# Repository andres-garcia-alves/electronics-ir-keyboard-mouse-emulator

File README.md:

# IR Keyboard+Mouse Emulator

Electronic project for use a IR Remote Control to control a Home Theater PC (HTPC) based on Arduino PRO Micro.  
Schematics diagram + PCB diagram (KiCAD 9) and case 3D model (Blender) are also provided.

This project comes in two versions: `Allways On` and `Low Power`.  
**Very important**: the current status of the `Low Power` version is **not working**, maybe I'll give it another try in the future.

- The `Allways On` version provides an immediate response when a remote control button is pressed.  
However, the gadget will constantly draw approximately 35-40mA from the USB port.

- The `Low Power` version automatically powers down the device after 30 seconds of inactivity, and it powers back on upon receiving an IR signal.  
This allows the gadget's power consumption to drop 99% of the time to ~1mA (the consumption of the IR sensor, the only component that remains powered on).  
However, due to the power-up time and the wait for the PC to recognize the device, there is a slight delay before it can be used.  
A high-side topology is used to power down the Arduino.
  - Hardware Variant A: External connection with a USB-A cable to J1 (USB-A socket).  
    Use a 2-strand cable from J2 (2-pins header) to the USB jack of Arduino for **data only** (D+/D-).
  - Hardware Variant B: External connection with a USB-B mini/micro cable to Arduino.  
    Cut the VCC wire of USB-B cable and pass it through J1 (2-pins header).

&nbsp;

General commands:
- Key Lock/Unlock (to avoid collition with regular TV usage).
- Key Esc
- Key Close (close current program)
- Mouse Change Speed
- Mouse Left Click
- Mouse Right Click
- Mouse MoveUp
- Mouse Move Right
- Mouse MoveDown
- Mouse MoveLeft

Media commands
- Media Player (open VLC media player)
- Media Play/Pause
- Media Stop
- Media Forward (moves forward 10 seconds)
- Media Rewind (moves backwards 10 seconds)
- Media Previous (moves forward 1 minute)
- Media Next (moves backwards 1 minute)
- Media Volume Mute
- Media Volume Up
- Media Volume Down

Miscellaneous commands
- MyPC (opens MyPC)
- Calculator (open Calculator);

Features:
- Dump of IR Codes (protocols: RC5, RC6, NEC, SONY, PANASONIC, LG, JVC, WHYNTER)

Benchmarks:

| Arduino PRO Micro                 | Tipical consumption |
|-----------------------------------|---------------------|
| Normal mode                       |            37-38 mA |
| ADC + SPI + TWI disabled          |            35-36 mA |
| USB detach + Clock @2 MHz         |            19-20 mA |
| USB detach + SLEEP_MODE_PWR_DOWN  |              4-5 mA |

I am currently working on incorporating a hardware low-power version.

&nbsp;

The `Allways ON` version uses the following electronic components:
- 1 x Arduino PRO Micro
- 1 x IR Receiver VS1838
- 1 x LED 3mm
- 1 x 1k ohm resistor

The `Low Power` version uses the following electronic components:
- 1 x Arduino PRO Micro
- 1 x IR Receiver VS1838
- 1 x LED 3mm
- 1 x 1k ohm resistor
- 1 x 47k ohm resistor
- 2 x 10k ohm resistor
- 1 x 100k ohm resistor
- 2 x 4.7k ohm resistor
- 3 x 1N4148 schottky diode
- 1 x 10uF electrolitic capacitor
- 3 x BC547 PNP transistor
- 2 x BC557 NPN transistor
- 1 x USB Type-A female connector
- 1 x Bornier 2-pins / JST connector 2-pins

&nbsp;

### Version Allways On

| Breadboard                                            | Assembly                                              |
|-------------------------------------------------------|-------------------------------------------------------|
|            |              |

| Schematics Diagram                                    | PCB Diagram                                           |
|-------------------------------------------------------|-------------------------------------------------------|
|    |           |

| PCB Render 3D                                         | PCB Render 3D                                         |
|-------------------------------------------------------|-------------------------------------------------------|
|   |    |

| Case 3D Model                                         | Project Final                                         |
|-------------------------------------------------------|-------------------------------------------------------|
|         |                     |

&nbsp;

### Version Low-Power-B

| Breadboard                                            | Assembly                                              |
|-------------------------------------------------------|-------------------------------------------------------|
|           |          |

| Assembly                                              | Assembly                                              |
|-------------------------------------------------------|-------------------------------------------------------|
|          |          |

| Schematics Diagram                                    | PCB Diagram                                           |
|-------------------------------------------------------|-------------------------------------------------------|
|   |          |

| PCB Render 3D                                         | PCB Render 3D                                         |
|-------------------------------------------------------|-------------------------------------------------------|
|  |   |

| Case 3D Model                                         | Project Final                                         |
|-------------------------------------------------------|-------------------------------------------------------|
|        |                     |

See 'Rescources' sub-folder for more pictures & videos of the project.

&nbsp;

### Version History

v1.00 (2025.12.18) - Initial release.  
v1.01 (2025.12.19) - Adding case 3D model.  
v1.02 (2025.12.22) - Update schematics and PCB.  
v1.03 (2025.12.29) - Firmware refactor for code clean-up.  
v1.04 (2026.01.02) - Adding Low-Power-A version protoboard & schematics.  
v1.05 (2026.01.03) - Adding Low-Power-A version firmware.  
v1.06 (2026.01.04) - Adding Low-Power-A version PCB.  
v1.07 (2026.01.04) - Adding Low-Power-A case 3D model.  
v1.08 (2026.01.06) - Minor fixes on Low-Power-A case 3D model.  
v1.09 (2026.01.09) - Minor fixes on Low-Power-A PCB.  
v1.10 (2026.01.14) - Adding Low-Power-B version schematics & PCB.  
v1.11 (2026.01.15) - Adding Low-Power-B 3D model.  
v1.12 (2026.01.18) - Minor fixes on Low-Power-B 3D model.  

&nbsp;

This source code is licensed under GPL v3.0  
Please send me your feedback about this project: andres.garcia.alves@gmail.com

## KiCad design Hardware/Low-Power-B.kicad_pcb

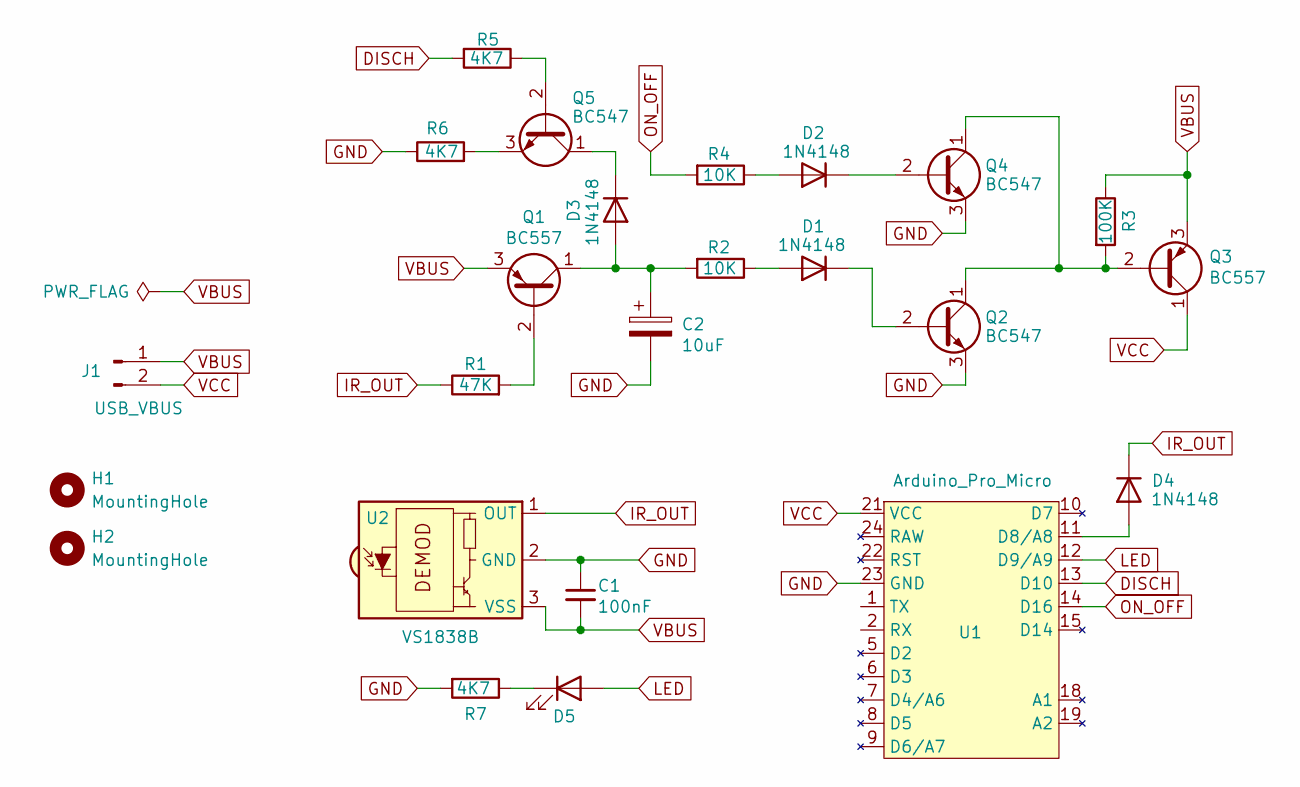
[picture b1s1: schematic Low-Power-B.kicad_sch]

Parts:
C1: 100nF; C_Disc_D6.0mm_W2.5mm_P5.00mm; Voltage 1kV; Tolerance 100%
C2: 10uF; CP_Radial_D5.0mm_P2.50mm
D1, D2, D3, D4: 1N4148; D_DO-35_SOD27_P7.62mm_Horizontal
D5: LED; LED_D5.0mm
H1, H2: MountingHole; MountingHole_2.2mm_M2_ISO7380
J1: USB_VBUS; JST_EH_B2B-EH-A_1x02_P2.50mm_Vertical
Q1, Q3: BC557; TO-92_Inline_Wide
Q2, Q4, Q5: BC547; TO-92_Inline_Wide
R1: 47K; R_Axial_DIN0207_L6.3mm_D2.5mm_P2.54mm_Vertical
R2: 10K; R_Axial_DIN0207_L6.3mm_D2.5mm_P7.62mm_Horizontal
R3: 100K; R_Axial_DIN0207_L6.3mm_D2.5mm_P2.54mm_Vertical
R4: 10K; R_Axial_DIN0207_L6.3mm_D2.5mm_P2.54mm_Vertical
R5, R6: 4K7; R_Axial_DIN0207_L6.3mm_D2.5mm_P2.54mm_Vertical
R7: 4K7; R_Axial_DIN0204_L3.6mm_D1.6mm_P7.62mm_Horizontal
U1: Arduino_Pro_Micro
U2: VS1838B; Vishay_MINICAST-3Pin

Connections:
DISCH: R5.2, U1.13 (D10)
GND: C1.1, C2.2, Q2.3 (E), Q4.3 (E), R6.1, R7.2, U1.3 (GND), U1.4 (GND), U1.23 (GND), U2.2 (GND)
IR_OUT: D4.1 (K), R1.1, U2.1 (OUT)
LED: D5.2 (A), U1.12 (D9/A9)
unnamed: D1.2 (A), R2.1
unnamed: D1.1 (K), Q2.2 (B)
unnamed: D2.2 (A), R4.1
unnamed: D2.1 (K), Q4.2 (B)
unnamed: C2.1, D3.2 (A), Q1.1 (C), R2.2
unnamed: D3.1 (K), Q5.1 (C)
unnamed: D4.2 (A), U1.11 (D8/A8)
unnamed: D5.1 (K), R7.1
unnamed: Q1.2 (B), R1.2
unnamed: Q2.1 (C), Q3.2 (B), Q4.1 (C), R3.2
unnamed: Q5.2 (B), R5.1
unnamed: Q5.3 (E), R6.2
ON_OFF: R4.2, U1.14 (D16)
VBUS: C1.2, J1.1, Q1.3 (E), Q3.3 (E), R3.1, U2.3 (VSS)
VCC: J1.2, Q3.1 (C), U1.21 (VCC)

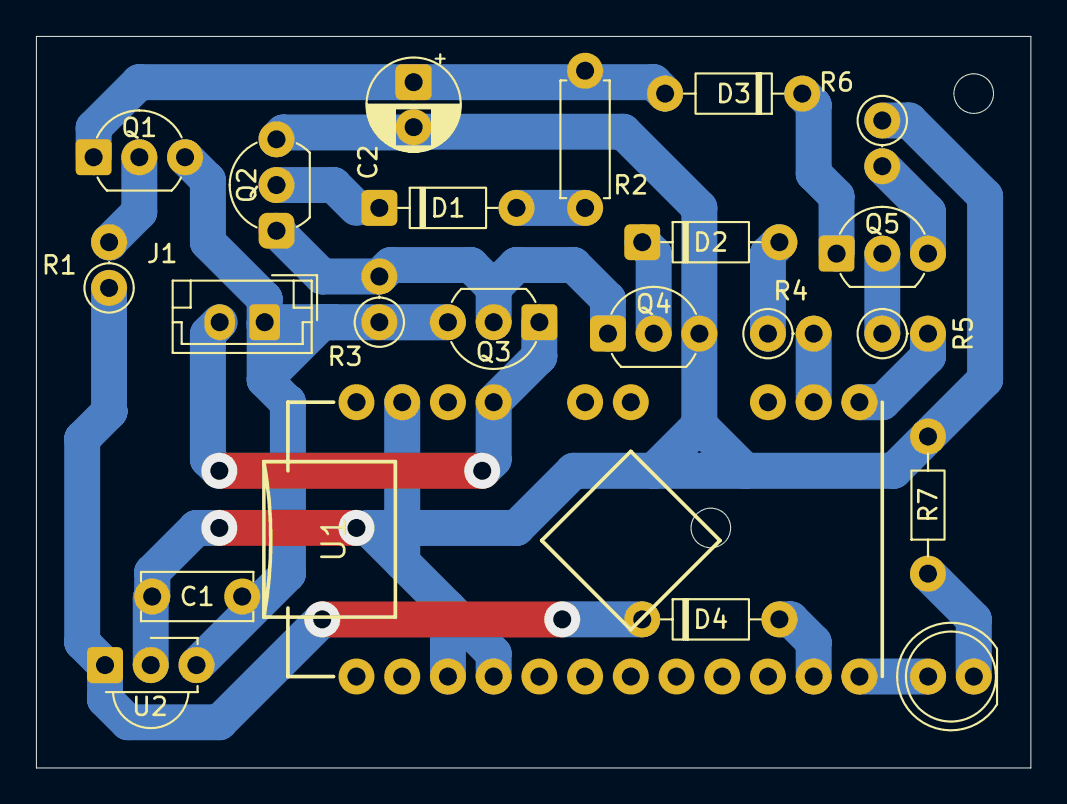
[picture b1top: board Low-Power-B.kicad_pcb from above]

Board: 2 copper layers, 55.2 x 40.6 mm, 24 parts (0 on the bottom side), 19 nets.

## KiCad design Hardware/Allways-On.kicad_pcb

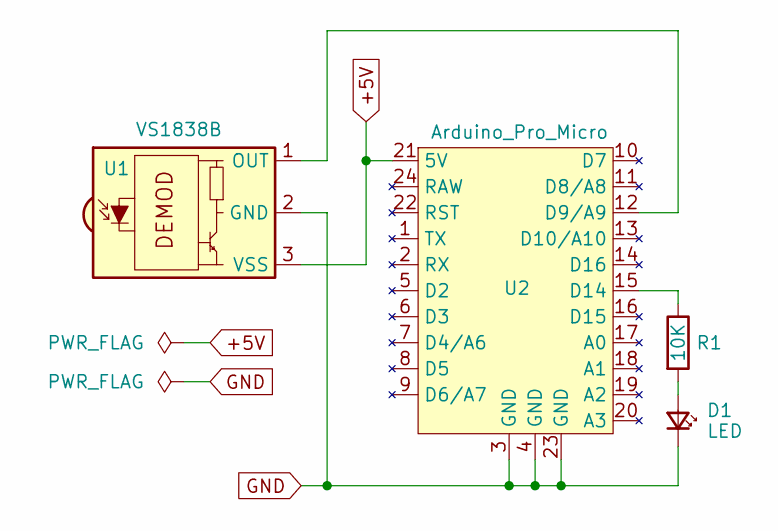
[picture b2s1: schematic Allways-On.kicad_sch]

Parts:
D1: LED; LED_D3.0mm
R1: 10K; R_Axial_DIN0204_L3.6mm_D1.6mm_P5.08mm_Horizontal
U1: VS1838B; Vishay_MINICAST-3Pin
U2: Arduino_Pro_Micro

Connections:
+5V: U1.3 (VSS), U2.21 (5V)
GND: D1.1 (K), U1.2 (GND), U2.3 (GND), U2.4 (GND), U2.23 (GND)
unnamed: D1.2 (A), R1.2
unnamed: U1.1 (OUT), U2.12 (D9/A9)
unnamed: R1.1, U2.15 (D14)

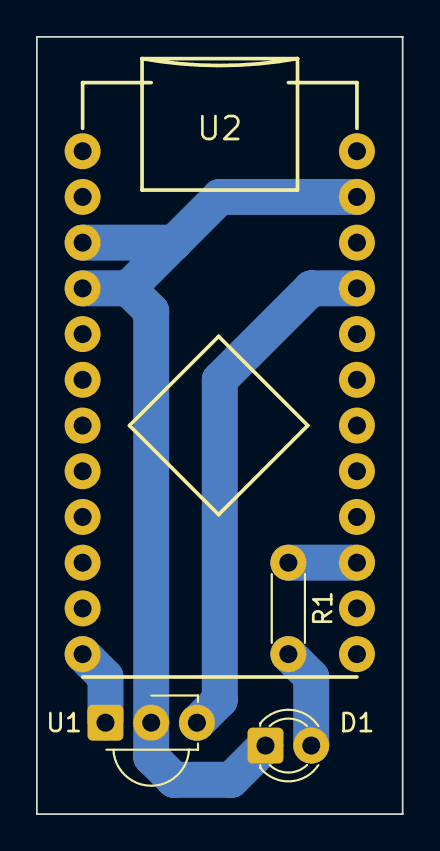
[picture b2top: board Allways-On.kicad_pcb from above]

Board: 2 copper layers, 20.3 x 43.2 mm, 4 parts (0 on the bottom side), 5 nets.

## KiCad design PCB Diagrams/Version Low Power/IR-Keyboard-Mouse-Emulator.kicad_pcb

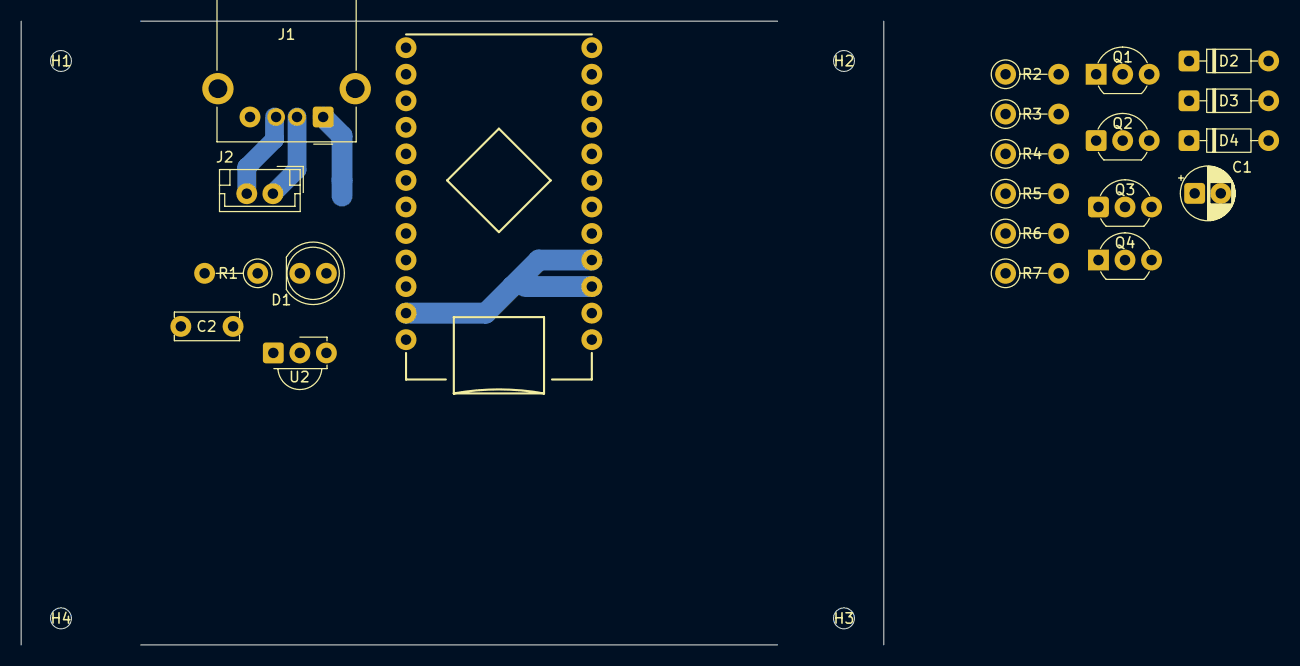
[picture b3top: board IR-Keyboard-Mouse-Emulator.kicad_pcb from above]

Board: 2 copper layers, 25 parts (0 on the bottom side), 19 nets.

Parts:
C1: 10uF; CP_Radial_D5.0mm_P2.50mm
C2: 100nF; C_Disc_D6.0mm_W2.5mm_P5.00mm
D1: LED; LED_D5.0mm
D2, D3, D4: 1N5817; D_DO-35_SOD27_P7.62mm_Horizontal
H1, H2, H3, H4: MountingHole; MountingHole_2mm
J1: USB_A; USB_A_Molex_67643_Horizontal
J2: 01x02; JST_EH_B2B-EH-A_1x02_P2.50mm_Vertical
Q1, Q3: BC557; TO-92_Inline_Wide
Q2, Q4: BC547; TO-92_Inline_Wide
R1: 1K; R_Axial_DIN0207_L6.3mm_D2.5mm_P5.08mm_Vertical
R2: 47K; R_Axial_DIN0207_L6.3mm_D2.5mm_P5.08mm_Vertical
R3, R5: 10K; R_Axial_DIN0207_L6.3mm_D2.5mm_P5.08mm_Vertical
R4: 100K; R_Axial_DIN0207_L6.3mm_D2.5mm_P5.08mm_Vertical
R6, R7: 4.7K; R_Axial_DIN0207_L6.3mm_D2.5mm_P5.08mm_Vertical
U1: Arduino_Pro_Micro
U2: VS1838B; Vishay_MINICAST-3Pin

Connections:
+5V: C2.2, J1.1 (VBUS), Q1.3 (E), Q3.3 (E), R4.1, U2.3 (VSS)
DISCH: R6.1, U1.7 (D4/A6)
GND: C1.2, C2.1, J1.4 (GND), J1.5 (Shield), Q2.3 (E), R1.2, R7.1, U1.3 (GND), U1.4 (GND), U1.23 (GND), U2.2 (GND)
IR_OUT: R2.1, U2.1 (OUT)
unnamed: D1.2 (A), U1.15 (D14)
unnamed: D1.1 (K), R1.1
unnamed: D2.2 (A), R3.1
unnamed: D2.1 (K), D3.1 (K), Q2.2 (B)
unnamed: D3.2 (A), R5.1
unnamed: C1.1, D4.2 (A), Q1.1 (C), R3.2
unnamed: D4.1 (K), Q4.1 (C)
unnamed: J1.3 (D+), J2.2
unnamed: J1.2 (D-), J2.1
unnamed: Q1.2 (B), R2.2
unnamed: Q2.1 (C), Q3.2 (B), R4.2
unnamed: Q4.2 (B), R6.2
unnamed: Q4.3 (E), R7.2
ON_OFF: R5.2, U1.8 (D5)
VCC: Q3.1 (C), U1.21 (VCC)

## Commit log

2025-12-19 adding 3D Model
2025-12-19 adding case 3D model
2025-12-20 update project structure
2025-12-22 update schematics and pcb
2025-12-29 firmware refactor for code clean-up
2026-01-03 Adding Low Power protoboard & schematics diagram
2026-01-03 Adding low-power firmware
2026-01-04 Adding low-power version PCB
2026-01-04 Adding low-power case 3D model
2026-01-07 Minor fixes on low-power case 3D model
2026-01-09 Minor fixes on low-power PCB
2026-01-13 Adding 'Resources' for Low-Power version
2026-01-14 Minor fixes on allways-on PCB
2026-01-14 Adding Low-Power-B version schematics & PCB
2026-01-15 Adding Low-Power-B 3D model
2026-01-18 Minor fixes on Low-Power-B 3D model
2026-02-02 Update Tracks
